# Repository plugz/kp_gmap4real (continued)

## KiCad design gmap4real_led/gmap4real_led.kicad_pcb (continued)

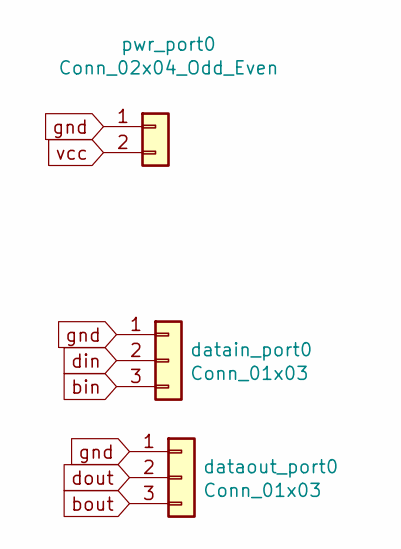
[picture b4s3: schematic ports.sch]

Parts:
datain_port0: Conn_01x03; PinHeader_1x03_P2.54mm_Vertical
dataout_port0: Conn_01x03; PinHeader_1x03_P2.54mm_Vertical
pwr_port0: Conn_02x04_Odd_Even; PinHeader_1x02_P2.54mm_Vertical

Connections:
bin: datain_port0.3; also elsewhere on the board
dout: dataout_port0.2; also elsewhere on the board
gnd: datain_port0.1, dataout_port0.1, pwr_port0.1; also elsewhere on the board
vcc: pwr_port0.2; also elsewhere on the board

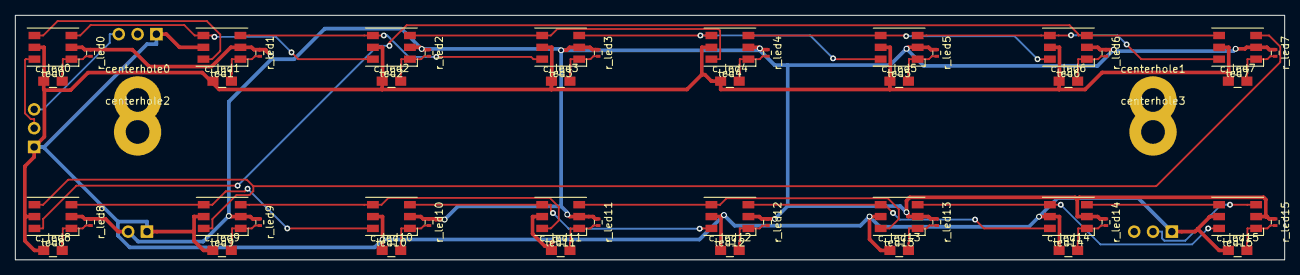
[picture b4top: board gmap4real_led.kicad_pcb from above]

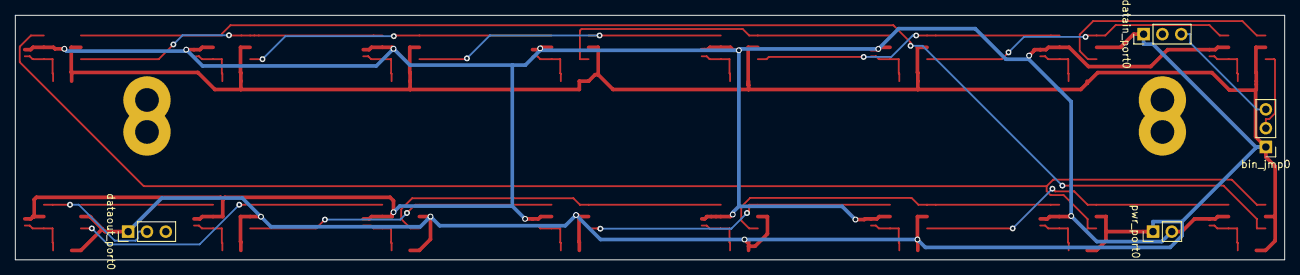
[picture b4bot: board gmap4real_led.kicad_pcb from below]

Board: 2 copper layers, 171.5 x 33.0 mm, 56 parts (4 on the bottom side), 37 nets.

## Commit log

2020-03-06 init commit
2020-03-06 add gmap4real_b files
2020-03-06 add gmap4real_f files
2020-03-06 add gmap4real_led files
2020-03-06 add gmap4real_teensy files
2020-03-06 add NOTES.txt
2020-03-09 smaller PCBs
2020-03-10 button: even smaller
2020-03-10 teensy: fix select pin conflict
2020-03-10 teensy: simplify (no agnd to buttons, no agnd to i2c port)
2020-03-10 add some buy quantities
